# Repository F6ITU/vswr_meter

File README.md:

# vswr_meter
PD0LEW reflectometer fork

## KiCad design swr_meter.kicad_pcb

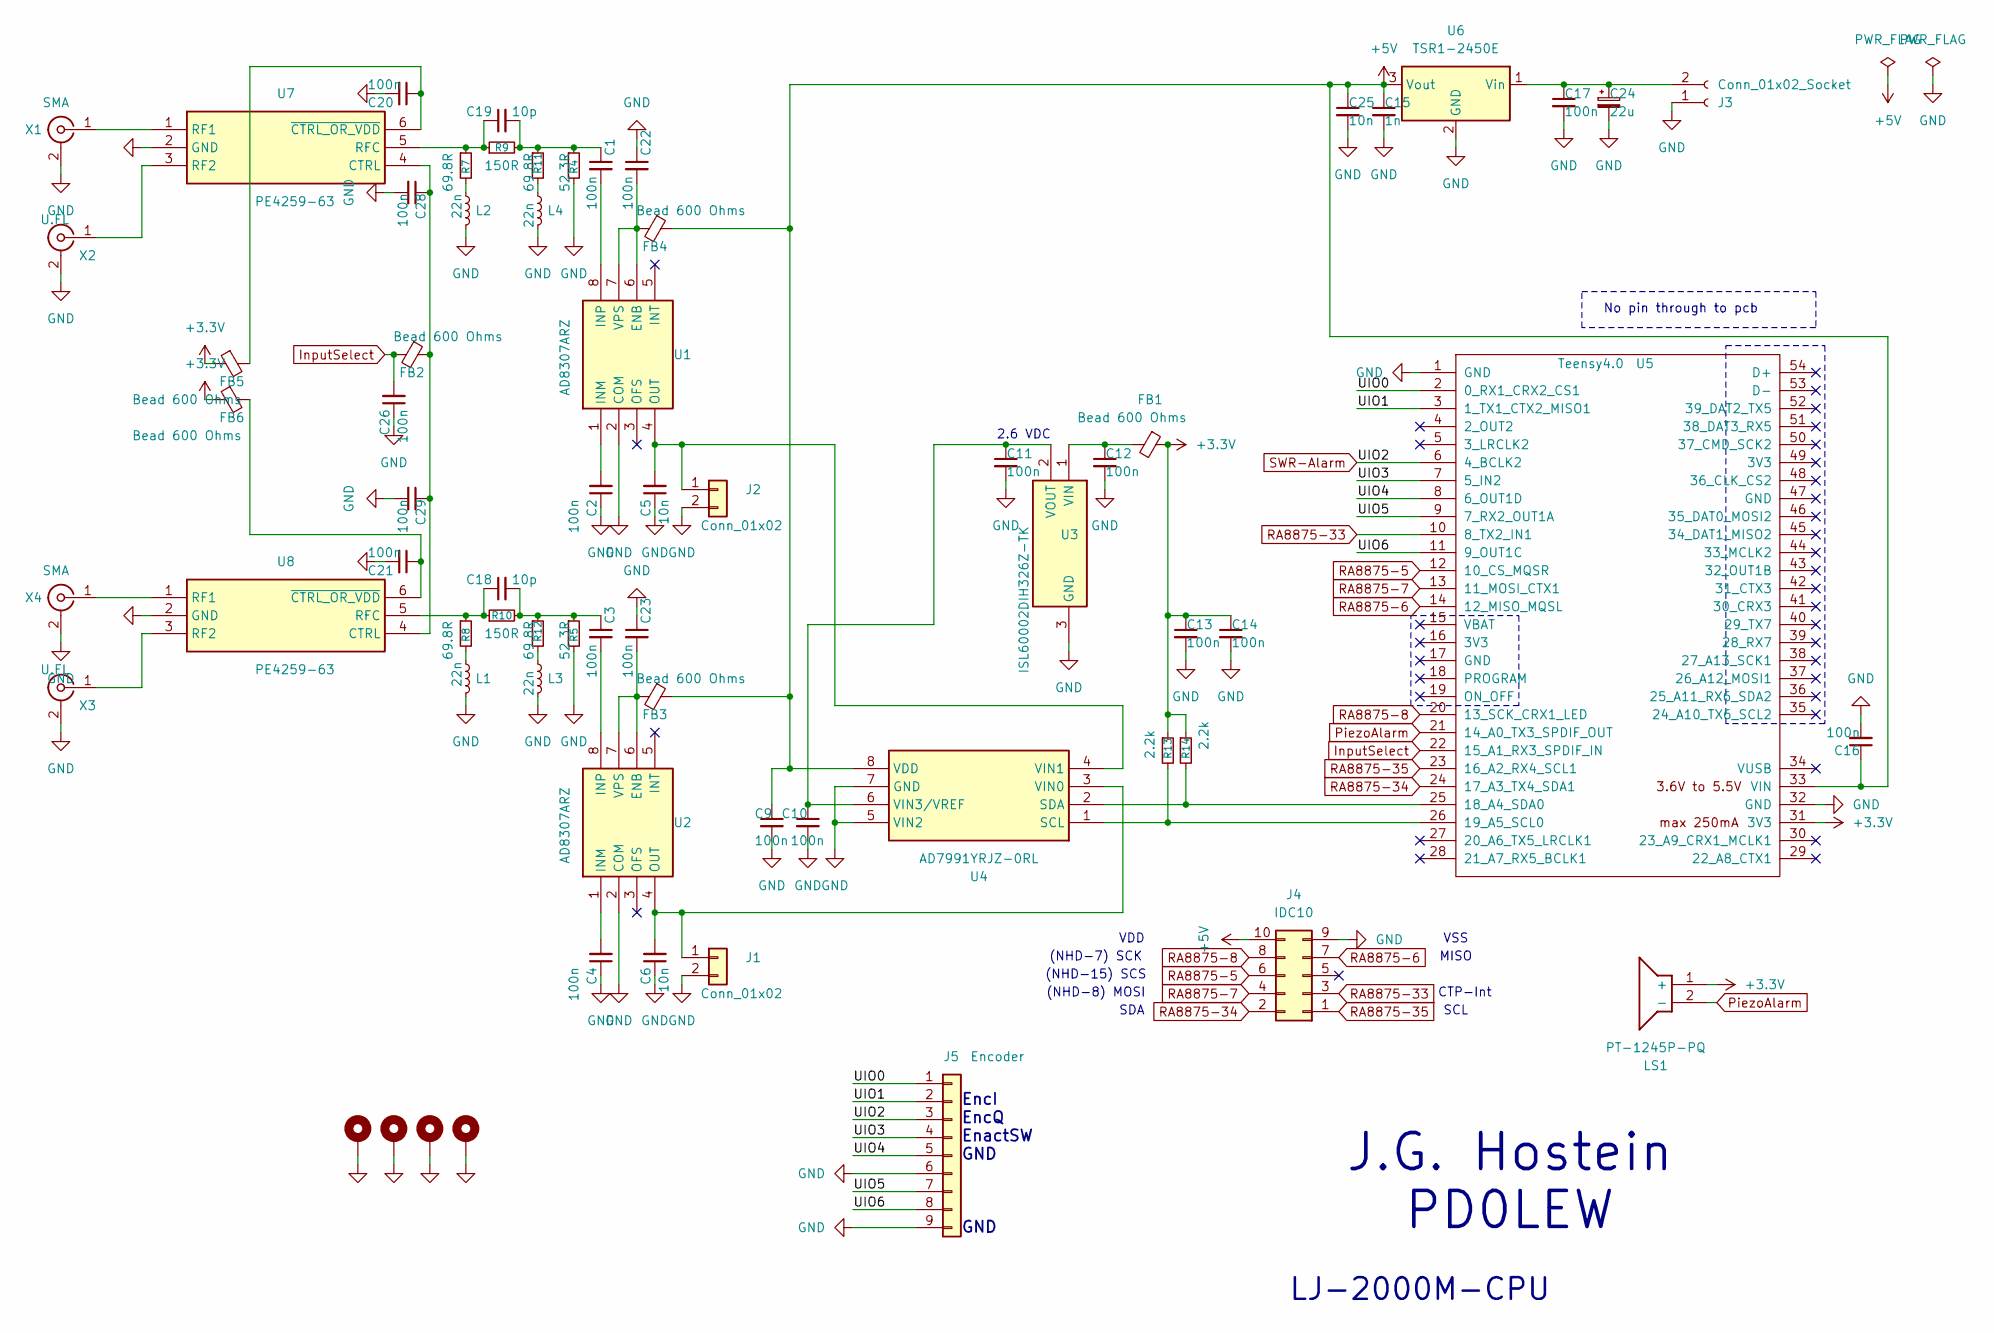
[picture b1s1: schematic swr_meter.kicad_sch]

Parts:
C1, C2, C3, C4, C20, C21, C22, C23, C28, C29: 100n; C_0603_1608Metric_Pad1.08x0.95mm_HandSolder
C5, C6: 10n; C_0603_1608Metric_Pad1.08x0.95mm_HandSolder
C9, C10, C11, C12, C13, C14, C16, C17, C26: 100n; C_0805_2012Metric_Pad1.18x1.45mm_HandSolder
C15: 1n; C_0805_2012Metric_Pad1.18x1.45mm_HandSolder
C18, C19: 10p; C_0603_1608Metric_Pad1.08x0.95mm_HandSolder
C24: 22u; CP_Elec_4x3
C25: 10n; C_0805_2012Metric_Pad1.18x1.45mm_HandSolder
FB1, FB2, FB3, FB4, FB5, FB6: Bead 600 Ohms; L_0805_2012Metric_Pad1.05x1.20mm_HandSolder
H201, H202, H203, H204: MountingHole_Pad; MountingHole_3.2mm_M3_ISO14580_Pad_TopBottom
J1, J2: Conn_01x02; Molex_KK-254_AE-6410-02A_1x02_P2.54mm_Vertical
J3: Conn_01x02_Socket; AMASS_XT30U-F_1x02_P5.0mm_Vertical
J4: IDC10; IDC-Header_2x05_P2.54mm_Vertical
J5: Encoder; Molex_KK-254_AE-6410-09A_1x09_P2.54mm_Vertical
L1, L2, L3, L4: 22n; L_0805_2012Metric_Pad1.05x1.20mm_HandSolder
LS1: PT-1245P-PQ; PT1245PPQ; Manufacturer_Part_Number PT-1245P-PQ
R4, R5: 52.3R; R_0603_1608Metric_Pad0.98x0.95mm_HandSolder
R7, R8, R11, R12: 69.8R; R_0603_1608Metric_Pad0.98x0.95mm_HandSolder
R9, R10: 150R; R_0603_1608Metric_Pad0.98x0.95mm_HandSolder
R13, R14: 2.2k; R_0805_2012Metric_Pad1.20x1.40mm_HandSolder
U1, U2: AD8307ARZ; SOIC127P600X175-8N; Mouser Part Number 584-AD8307ARZ-R
U3: ISL60002DIH326Z-TK; SOT95P237X112-3N; Mouser Part Number 968-ISL60002DIH326ZT
U4: AD7991YRJZ-0RL; SOT65P280X145-8N; Manufacturer_Part_Number AD7991YRJZ-0RL; Mouser Part Number 584-AD7991YRJZ-0R
U5: Teensy4.0; Teensy40
U6: TSR1-2450E; Converter_DCDC_TRACO_TSR1-xxxxE_THT
U7, U8: PE4259-63; SOT65P210X110-6N; Manufacturer_Part_Number PE4259-63
X1, X4: SMA; SMA_EDGE_NRW
X2, X3: U.FL; SMA_PINS

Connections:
+3.3V: C13.1, C14.1, FB1.1, FB5.1, FB6.1, LS1.1 (+), R13.1, R14.1, U5.31 (3V3)
+5V: C9.1, C15.1, C16.1, C25.1, FB3.1, FB4.1, J4.10, U4.8 (VDD), U5.33 (VIN), U6.3 (Vout); also elsewhere on the board
/UIO0: J5.1, U5.2 (0_RX1_CRX2_CS1)
/UIO1: J5.2, U5.3 (1_TX1_CTX2_MISO1)
/UIO3: J5.4, U5.7 (5_IN2)
/UIO4: J5.5, U5.8 (6_OUT1D)
/UIO5: J5.7, U5.9 (7_RX2_OUT1A)
/UIO6: J5.8, U5.11 (9_OUT1C)
GND: C2.1, C4.1, C5.1, C6.1, C9.2, C10.2, C11.2, C12.2, C13.2, C14.2, C15.2, C16.2, C17.2, C20.2, C21.2, C22.1, C23.1, C24.2, C25.2, C26.1, C28.2, C29.2, H201.1 (1_1), H202.1 (1_1), H203.1 (1_1), H204.1 (1_1), J1.2, J2.2, J3.1, J4.9, J5.6, J5.9, L1.2, L2.2, L3.2, L4.2, R4.2, R5.2, U1.2 (COM), U2.2 (COM), U3.3 (GND), U4.5 (VIN2), U4.7 (GND), U5.1 (GND), U5.32 (GND), U6.2 (GND), U7.2 (GND), U8.2 (GND), X1.2 (Ext), X2.2 (Ext), X3.2 (Ext), X4.2 (Ext); also elsewhere on the board
InputSelect: C26.2, FB2.2, U5.22 (15_A1_RX3_SPDIF_IN)
unnamed: C1.1, C19.2, R4.1, R9.2, R11.1
unnamed: C3.1, C18.2, R5.1, R10.2, R12.1
unnamed: C6.2, J1.1, U2.4 (OUT), U4.3 (VIN0)
unnamed: C5.2, J2.1, U1.4 (OUT), U4.4 (VIN1)
unnamed 14: C17.1, C24.1, J3.2, U6.1 (Vin); also elsewhere on the board
unnamed: L1.1, R8.2
unnamed: L2.1, R7.2
unnamed: L3.1, R12.2
unnamed: L4.1, R11.2
unnamed: C22.2, FB4.2, U1.6 (ENB), U1.7 (VPS)
unnamed: C2.2, U1.1 (INM)
unnamed: C1.2, U1.8 (INP)
unnamed: C23.2, FB3.2, U2.6 (ENB), U2.7 (VPS)
unnamed: C4.2, U2.1 (INM)
unnamed: C3.2, U2.8 (INP)
unnamed: C12.1, FB1.2, U3.1 (VIN)
unnamed: C10.1, C11.1, U3.2 (VOUT), U4.6 (VIN3/VREF)
unnamed: R13.2, U4.1 (SCL), U5.26 (19_A5_SCL0)
unnamed: R14.2, U4.2 (SDA), U5.25 (18_A4_SDA0)
unnamed: C28.1, C29.1, FB2.1, U7.4 (CTRL), U8.4 (CTRL)
unnamed: U7.1 (RF1), X1.1 (In)
unnamed: U7.3 (RF2), X2.1 (In)
unnamed: C19.1, R7.1, R9.1, U7.5 (RFC)
unnamed: C20.1, FB5.2, U7.6 (~CTRL_OR_VDD)
unnamed: U8.1 (RF1), X4.1 (In)
unnamed: U8.3 (RF2), X3.1 (In)
unnamed: C18.1, R8.1, R10.1, U8.5 (RFC)
unnamed: C21.1, FB6.2, U8.6 (~CTRL_OR_VDD)
PiezoAlarm: LS1.2 (-), U5.21 (14_A0_TX3_SPDIF_OUT)
RA8875-5: J4.6, U5.12 (10_CS_MQSR)
RA8875-6: J4.7, U5.14 (12_MISO_MQSL)
RA8875-7: J4.4, U5.13 (11_MOSI_CTX1)
RA8875-8: J4.8, U5.20 (13_SCK_CRX1_LED)
RA8875-33: J4.3, U5.10 (8_TX2_IN1)
RA8875-34: J4.2, U5.24 (17_A3_TX4_SDA1)
RA8875-35: J4.1, U5.23 (16_A2_RX4_SCL1)
SWR-Alarm: J5.3, U5.6 (4_BCLK2)

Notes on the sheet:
(NHD-8) MOSI
SDA
VDD
CTP-Int
SCL
(NHD-15) SCS
2.6 VDC
MISO
J.G. Hostein PD0LEW
VSS
No pin through to pcb
EncI EncQ EnactSW GND GND
LJ-2000M-CPU
(NHD-7) SCK

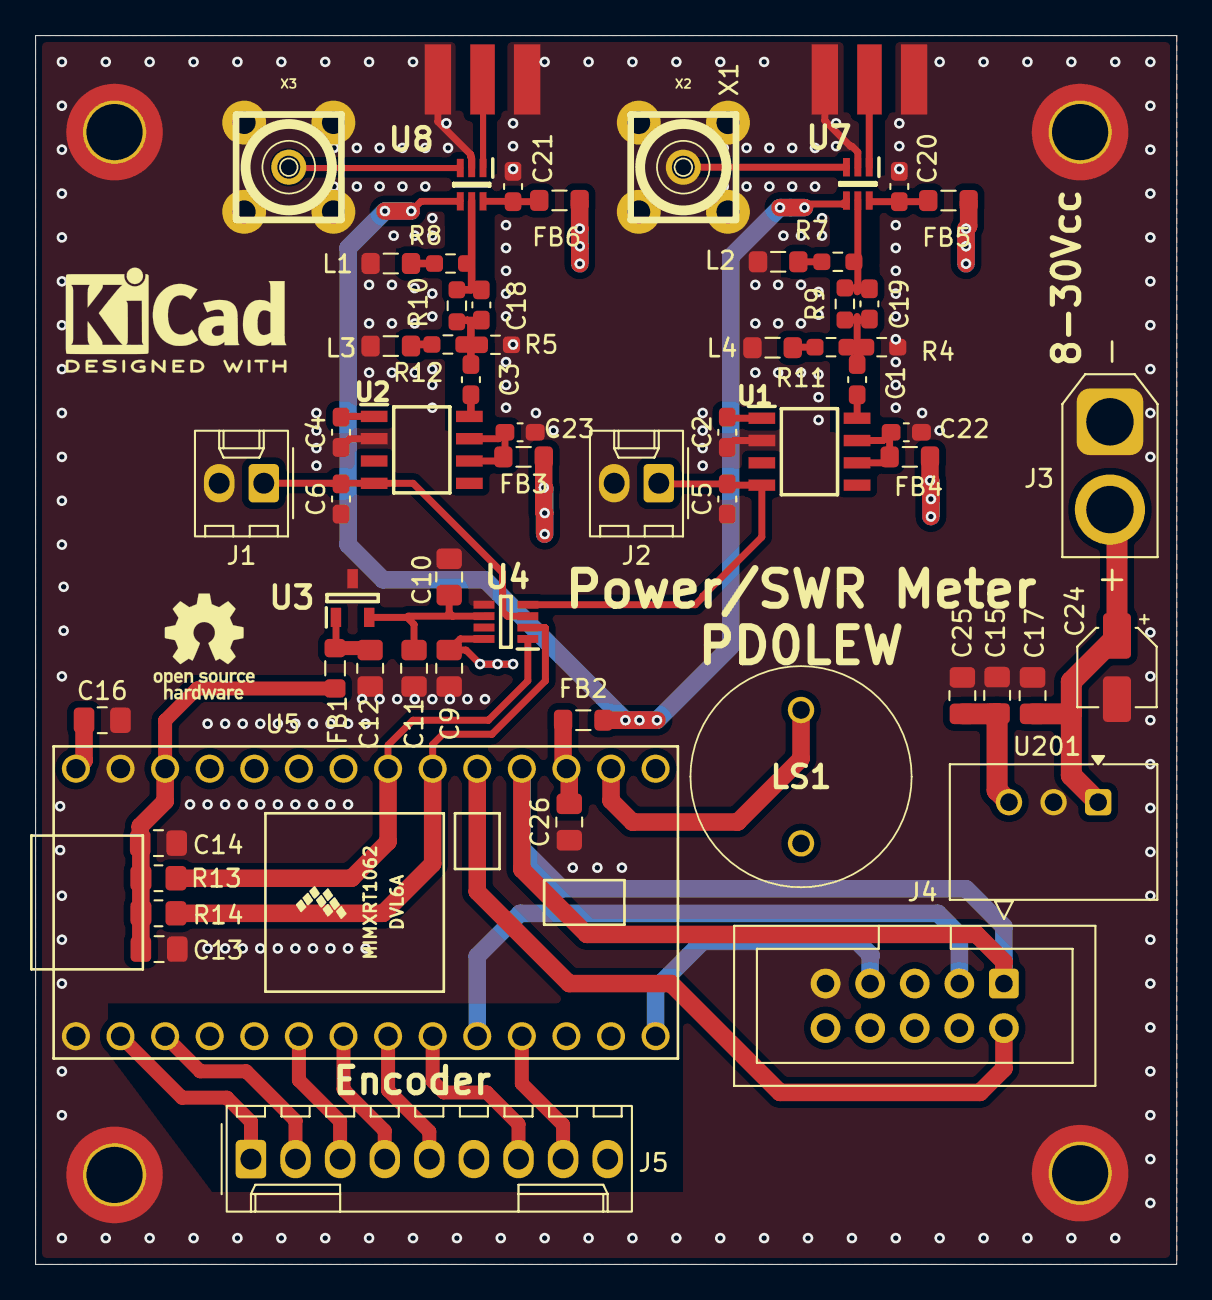
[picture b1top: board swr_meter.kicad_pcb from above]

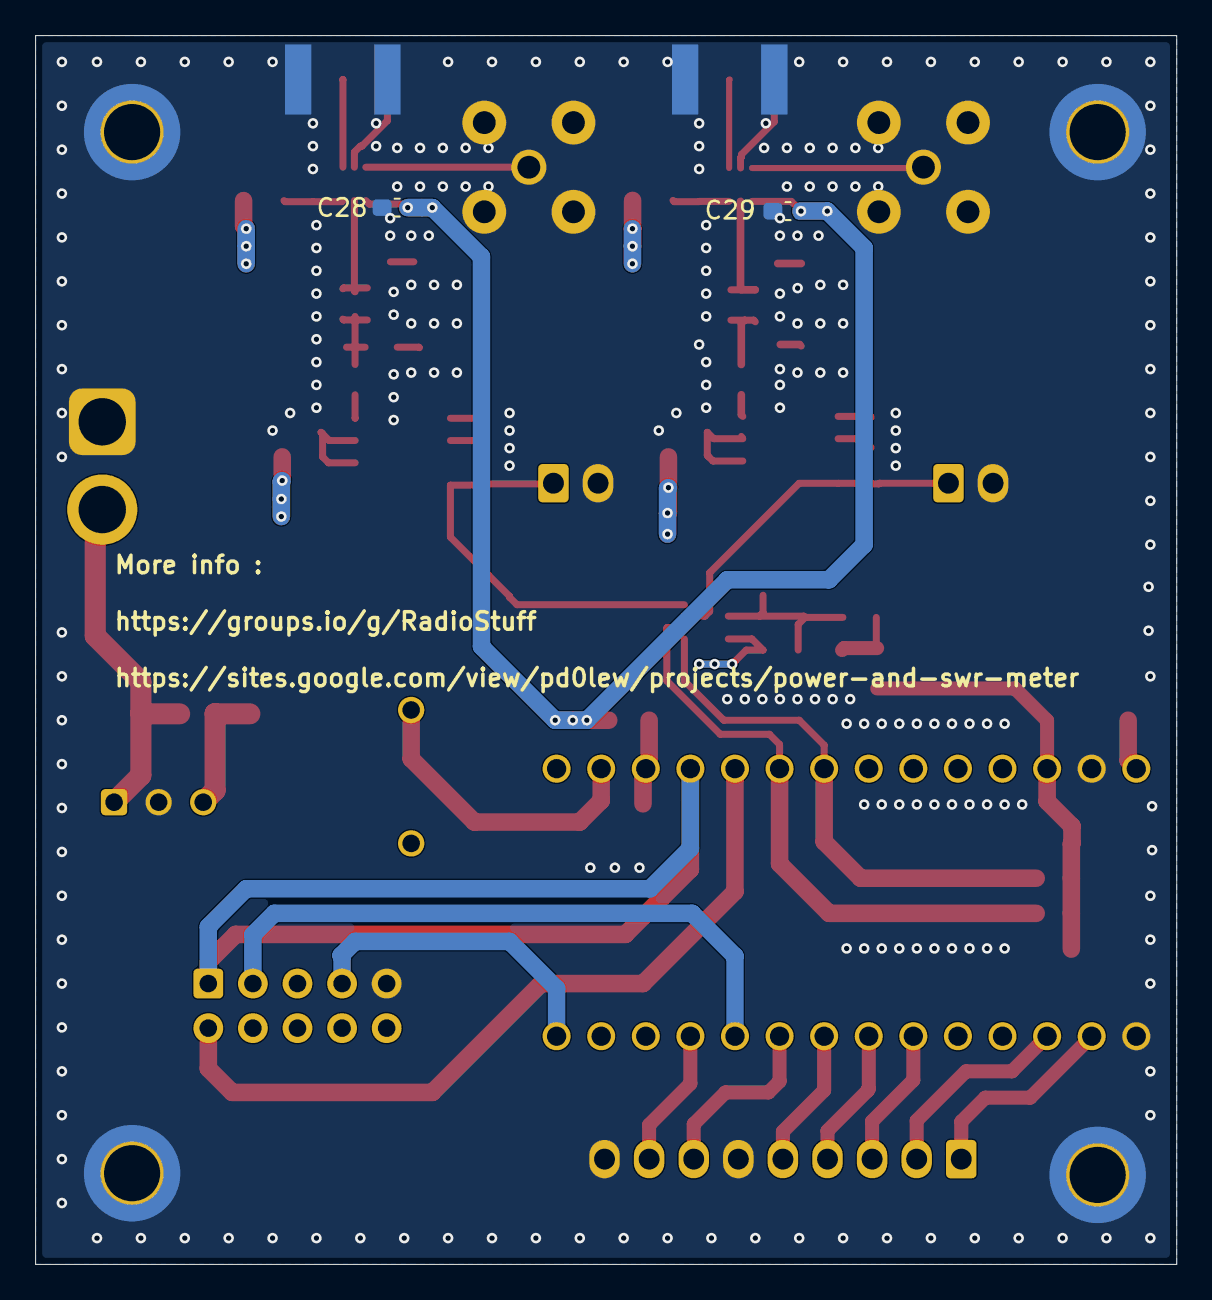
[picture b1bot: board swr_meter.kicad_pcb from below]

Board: 4 copper layers, 65.0 x 70.0 mm, 68 parts (2 on the bottom side), 47 nets.

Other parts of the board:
U201: TSR1-2450E; Converter_DCDC_TRACO_TSR1-xxxxE_THT

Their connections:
+5V: U201.3 (Vout); also elsewhere on the board
GND: U201.2 (GND); also elsewhere on the board
unnamed 14: U201.1 (Vin); also elsewhere on the board

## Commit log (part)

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2026-05-25 initial commit, kicad 10, w Gerbers, schematic, 3D render,doc, libs
2026-05-26 minor changes, silk cleaning, new ibom
